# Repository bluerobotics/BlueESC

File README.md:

BlueESC
=======

The BlueESC is a simple, open-source electronic speed controller for three-phase brushless motors. It is designed to run the [SimonK firmware](http://github.com/sim-/tgy) on an Atmega8 microcontroller.

The hardware is licensed under GPLv3. It was inspired by and draws from other open-source ESC projects including [AfroESC](https://code.google.com/p/afrodevices/), [WiiESC](https://code.google.com/p/wii-esc/), and others. We owe a big thanks to everyone who has shared their open-source ESC designs and firmware.

We also thank Bernhard Konze and SimonK for the [tgy firmware](http://github.com/sim-/tgy). Please see the firmware license at the top of [tgy.asm](https://github.com/bluerobotics/tgy/blob/master/tgy.asm). The firmware configuration files for the BlueESC are maintained in [our fork of the tgy project](http://github.com/bluerobotics/tgy).

##Features

* Atmega8 microcontroller
* PWM and I2C signal interfaces
* 5-22 volt input (2-5s lipo)
* Reprogrammable via PWM pin using bootloader (usblinker)
* Status and warning LED indicators
* Sensors for voltage, current, temperature, and RPM
* No battery-eliminator-circuit (BEC)
* N-Channel MOSFETs

##Current Generation: Rev. 5-8

The current major revision is designed to work with the [BlueRobotics T100 Thruster](http://www.bluerobotics.com/thruster/). It is highly compact and is potted in an aluminum enclosure that acts as a heat sink. The board is built with two 2-layer boards, one for the power electronics and one for logic. The boards are connected by headers. This allows components to be placed on three sides, simplifies design, and minimizes cost.

###Features

* Hall effect current sense IC (ACS711EX)
* Thermistor temperature sensor (10K)

###Specifications

* 6-22 volt input
* 25 amps continuous current (air)
* 35+ amps continuous current (water)
* 400 uF decoupling capacitance
* Enclosure diameter: 40 mm (1.58")
* Enclosure length: 18.5 mm (0.73")

###Design Files

**Schematic:** [BlueESC.pdf](https://github.com/bluerobotics/BlueESC/raw/master/BlueESC/BlueESC.pdf)

See repository for up-to-date EagleCAD schematic and board layout.

##Firmware Compilation

The BlueESC uses the [tgy firmware located in the BlueRobotics fork](https://github.com/bluerobotics/tgy).

*Mac:* (Uses Homebrew)

```bash
brew update
brew install avra
make blueesc.hex
```

##Initial Firmware Flashing

The BlueESC can be flashed using any AVR ISP programmer.

```bash
avrdude -c [programmer] -p m8 -U flash:w:blueesc.hex:i 
```

The fuses should be set per the instructions in the [tgy](http://github.com/sim-/tgy) instructions.

```bash
avrdude -c [programmer] -p m8 -U lfuse:w:0x3f:m -U hfuse:w:0xca:m
```

The Rev5 version of the board does not include an ISP header or pads. The microcontroller must be flashed with a special tool that connects directly to the microcontroller pins. Make sure that the board is powered when programming.

##Firmware Flashing Through Bootloader

Once the ESC has had the firmware (including bootloader) flashed the first time, it can be reprogrammed subsequently through the PWM input pin using a programmer like the [Turnigy USB Linker](http://www.hobbyking.com/hobbyking/store/__10628__turnigy_usb_linker_for_aquastar_super_brain.html). This can be done through the Makefile in the **tgy** project as follows.

```bash
make program_tgy_blueesc
```

It can also be done with avrdude and the compiled hex files as follows.

```bash
avrdude -c stk500v2 -b 19200 -P [programmer port] -p m8 -U flash:w:blueesc.hex:i
```

##I2C Commands and Address

*Please also see our [Arduino library for I2C ESC control](https://github.com/bluerobotics/Arduino_I2C_ESC).*

The I2C message format allows speed and direction to be set and voltage, current, rpm, temperature, and status to be requested.

###Speed Command (Register 0x00-0x01)
* cmd: Command, sent as int16_t. Full range, negative for reverse, positive for forward.
  * Forward: 0 to 32767
  * Reverse: 0 to -32767

####Bytes
* Byte 0: throttle_h
* Byte 1: throttle_l

###Sensor Data (Register 0x02-0x0A)
* pulse_count: Commutation pulses since last request. Sent as uint16_t.
  * Calculate rpm with pulse_count/dt*60/motor_pole_count
* voltage: ADC measurement scaled to 16 bits
  * Calculate voltage with voltage/2016
* temperature: ADC measurement scaled to 16 bits
  * Calculate temperature with the Steinhart equation
* current: ADC measurement scaled to 16 bits
  * Calculate current with (current-32767)/891

####Bytes
* Byte 0: pulse_count_h
* Byte 1: pulse_count_l
* Byte 2: voltage_h
* Byte 3: voltage_l
* Byte 4: temperature_h
* Byte 5: temperature_l
* Byte 6: current_h
* Byte 7: current_l
* Byte 8: 0xab (identifier to check if ESC is alive)

##Releases

v1.0 - Rev5. Currently shipping.

v1.1 - Rev6. Added PWM pull-down resistor and low pass filter for current sense. Switched to SMT LEDs. No changes to Power Board.

##Video

I2C Demonstration:

Testing of Final Prototype:

Testing of First Prototype:

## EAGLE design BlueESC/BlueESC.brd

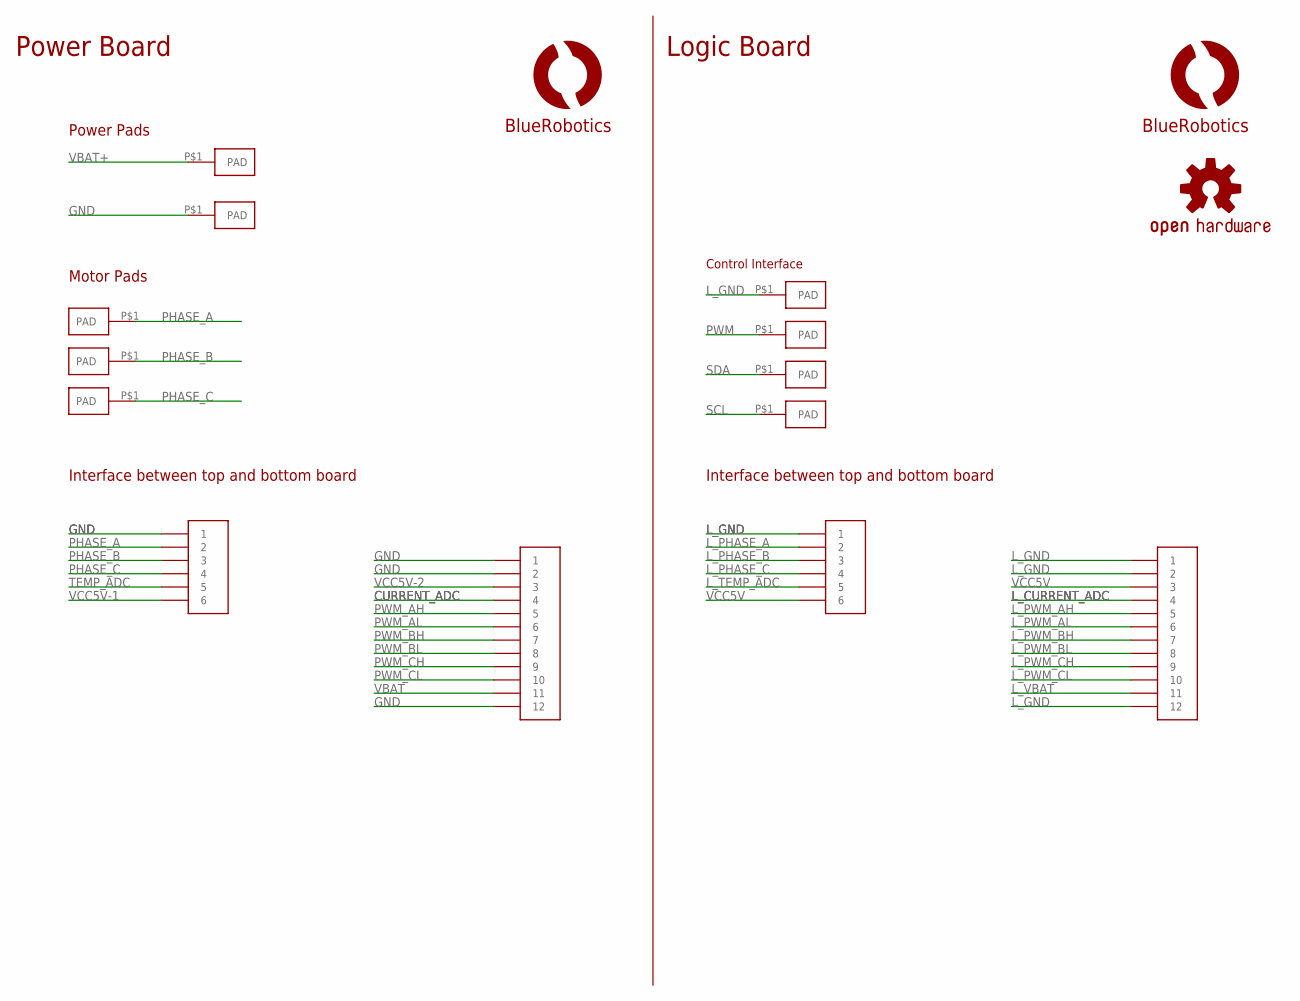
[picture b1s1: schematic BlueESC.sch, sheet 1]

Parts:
LOGO1: OSHW-LOGOS; OSHW-LOGO-S
U$1, U$2: PADPTH-MED; PAD-PTH-MED-1
U$4, U$16: HEADER-62MM; HEADER-2MM-6POS
U$5, U$6, U$7: PAD18AWG; PAD-PTH-18AWG-1
U$8, U$17: HEADER-122MM; HEADER-2MM-12POS
U$9: LOGOBR-LOGO-S; BR-LOGO-SMALL
U$10: LOGOBR-LOGO-M; BR-LOGO-MEDIUM
U$11, U$12, U$13, U$14: PAD1.5X3MM; PAD-1.5X3MM

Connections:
CURRENT_ADC: U$8.P$4 (4); also elsewhere on the board
GND: U$2.P$1, U$4.P$1 (1), U$8.P$1 (1), U$8.P$2 (2), U$8.P$12 (12); also elsewhere on the board
L_CURRENT_ADC: U$17.P$4 (4); also elsewhere on the board
L_GND: U$11.P$1, U$16.P$1 (1), U$17.P$1 (1), U$17.P$2 (2), U$17.P$12 (12); also elsewhere on the board
L_PHASE_A: U$16.P$2 (2); also elsewhere on the board
L_PHASE_B: U$16.P$3 (3); also elsewhere on the board
L_PHASE_C: U$16.P$4 (4); also elsewhere on the board
L_PWM_AH: U$17.P$5 (5); also elsewhere on the board
L_PWM_AL: U$17.P$6 (6); also elsewhere on the board
L_PWM_BH: U$17.P$7 (7); also elsewhere on the board
L_PWM_BL: U$17.P$8 (8); also elsewhere on the board
L_PWM_CH: U$17.P$9 (9); also elsewhere on the board
L_PWM_CL: U$17.P$10 (10); also elsewhere on the board
L_TEMP_ADC: U$16.P$5 (5); also elsewhere on the board
L_VBAT: U$17.P$11 (11); also elsewhere on the board
PHASE_A: U$4.P$2 (2), U$5.P$1; also elsewhere on the board
PHASE_B: U$4.P$3 (3), U$6.P$1; also elsewhere on the board
PHASE_C: U$4.P$4 (4), U$7.P$1; also elsewhere on the board
PWM: U$14.P$1; also elsewhere on the board
PWM_AH: U$8.P$5 (5); also elsewhere on the board
PWM_AL: U$8.P$6 (6); also elsewhere on the board
PWM_BH: U$8.P$7 (7); also elsewhere on the board
PWM_BL: U$8.P$8 (8); also elsewhere on the board
PWM_CH: U$8.P$9 (9); also elsewhere on the board
PWM_CL: U$8.P$10 (10); also elsewhere on the board
SCL: U$13.P$1; also elsewhere on the board
SDA: U$12.P$1; also elsewhere on the board
TEMP_ADC: U$4.P$5 (5); also elsewhere on the board
VBAT: U$8.P$11 (11); also elsewhere on the board
VBAT+: U$1.P$1; also elsewhere on the board
VCC5V: U$16.P$6 (6), U$17.P$3 (3); also elsewhere on the board
VCC5V-1: U$4.P$6 (6); also elsewhere on the board
VCC5V-2: U$8.P$3 (3); also elsewhere on the board

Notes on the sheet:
Power Pads
Motor Pads
Interface between top and bottom board
Control Interface
Power Board
Logic Board

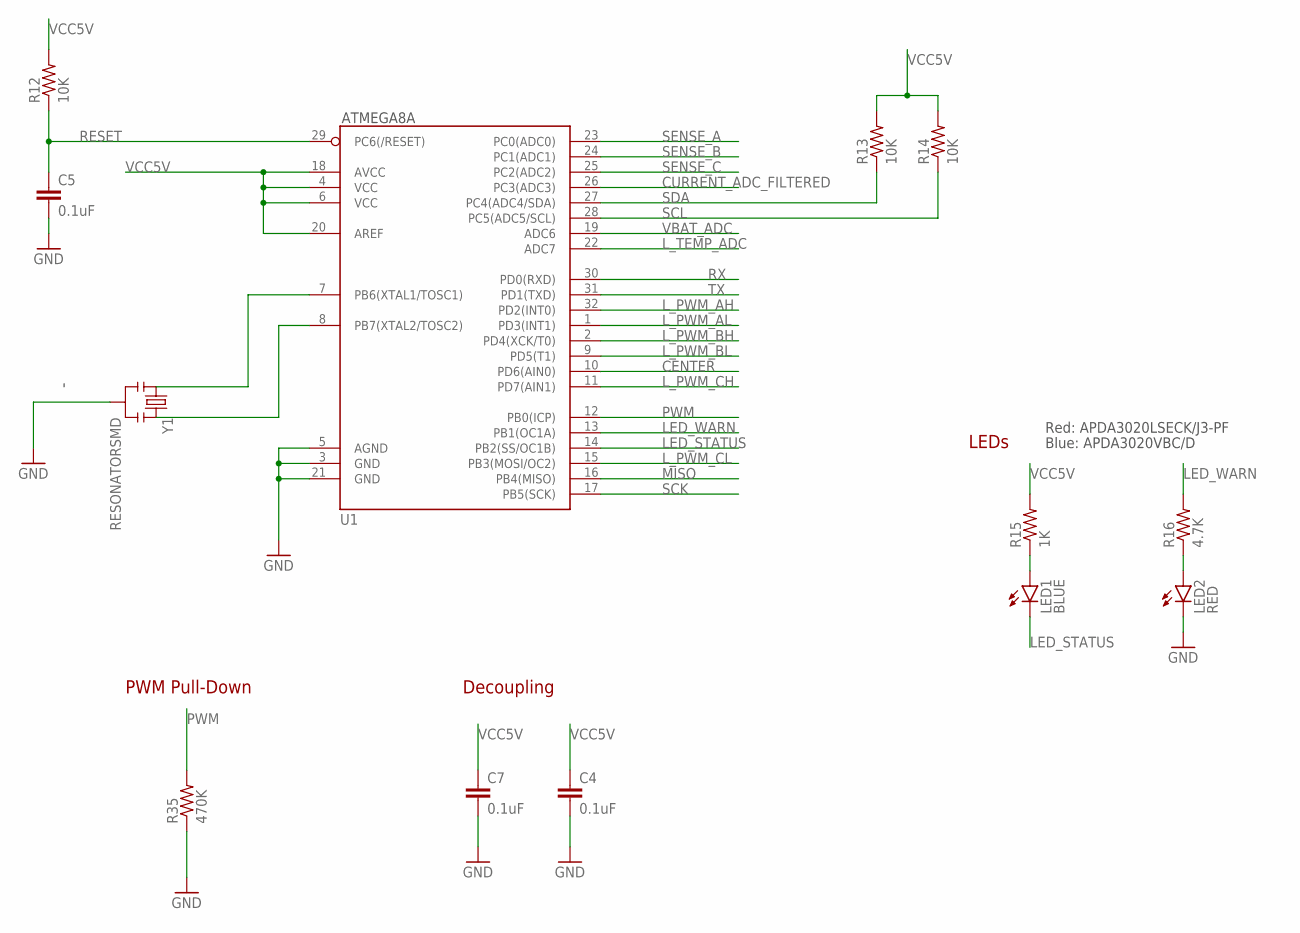
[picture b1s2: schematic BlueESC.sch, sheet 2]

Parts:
C4, C5, C7: 0.1uF; 0603-CAP
LED1: BLUE; SMT-LED-3X2-RA
LED2: RED; SMT-LED-3X2-RA
R12, R13, R14: 10K; 0603-RES
R15: 1K; 0603-RES
R16: 4.7K; 0603-RES
R35: 470K; 0603-RES
U1: ATMEGA168; TQFP32-08
Y1: RESONATORSMD; RESONATOR-SMD

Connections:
CENTER: U1.10 (PD6(AIN0)); also elsewhere on the board
CURRENT_ADC_FILTERED: U1.26 (PC3(ADC3)); also elsewhere on the board
LED_STATUS: LED1.2 (C), U1.14 (PB2(SS/OC1B))
LED_WARN: R16.2, U1.13 (PB1(OC1A))
L_GND: C4.2, C5.2, C7.2, LED2.2 (C), R35.1, U1.3 (GND), U1.5 (AGND), U1.21 (GND), Y1.2; also elsewhere on the board
L_PWM_AH: U1.32 (PD2(INT0)); also elsewhere on the board
L_PWM_AL: U1.1 (PD3(INT1)); also elsewhere on the board
L_PWM_BH: U1.2 (PD4(XCK/T0)); also elsewhere on the board
L_PWM_BL: U1.9 (PD5(T1)); also elsewhere on the board
L_PWM_CH: U1.11 (PD7(AIN1)); also elsewhere on the board
L_PWM_CL: U1.15 (PB3(MOSI/OC2)); also elsewhere on the board
L_TEMP_ADC: U1.22 (ADC7); also elsewhere on the board
MISO: U1.16 (PB4(MISO))
unnamed: LED2.1 (A), R16.1
unnamed: U1.7 (PB6(XTAL1/TOSC1)), Y1.1
unnamed: U1.8 (PB7(XTAL2/TOSC2)), Y1.3
unnamed: LED1.1 (A), R15.1
PWM: R35.2, U1.12 (PB0(ICP)); also elsewhere on the board
RESET: C5.1, R12.1, U1.29 (PC6(/RESET))
RX: U1.30 (PD0(RXD))
SCK: U1.17 (PB5(SCK))
SCL: R14.1, U1.28 (PC5(ADC5/SCL)); also elsewhere on the board
SDA: R13.1, U1.27 (PC4(ADC4/SDA)); also elsewhere on the board
SENSE_A: U1.23 (PC0(ADC0)); also elsewhere on the board
SENSE_B: U1.24 (PC1(ADC1)); also elsewhere on the board
SENSE_C: U1.25 (PC2(ADC2)); also elsewhere on the board
TX: U1.31 (PD1(TXD))
VBAT_ADC: U1.19 (ADC6); also elsewhere on the board
VCC5V: C4.1, C7.1, R12.2, R13.2, R14.2, R15.2, U1.4 (VCC), U1.6 (VCC), U1.18 (AVCC), U1.20 (AREF); also elsewhere on the board

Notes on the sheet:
ATMEGA8A
Decoupling
LEDs
Red: APDA3020LSECK/J3-PF
Blue: APDA3020VBC/D
PWM Pull-Down

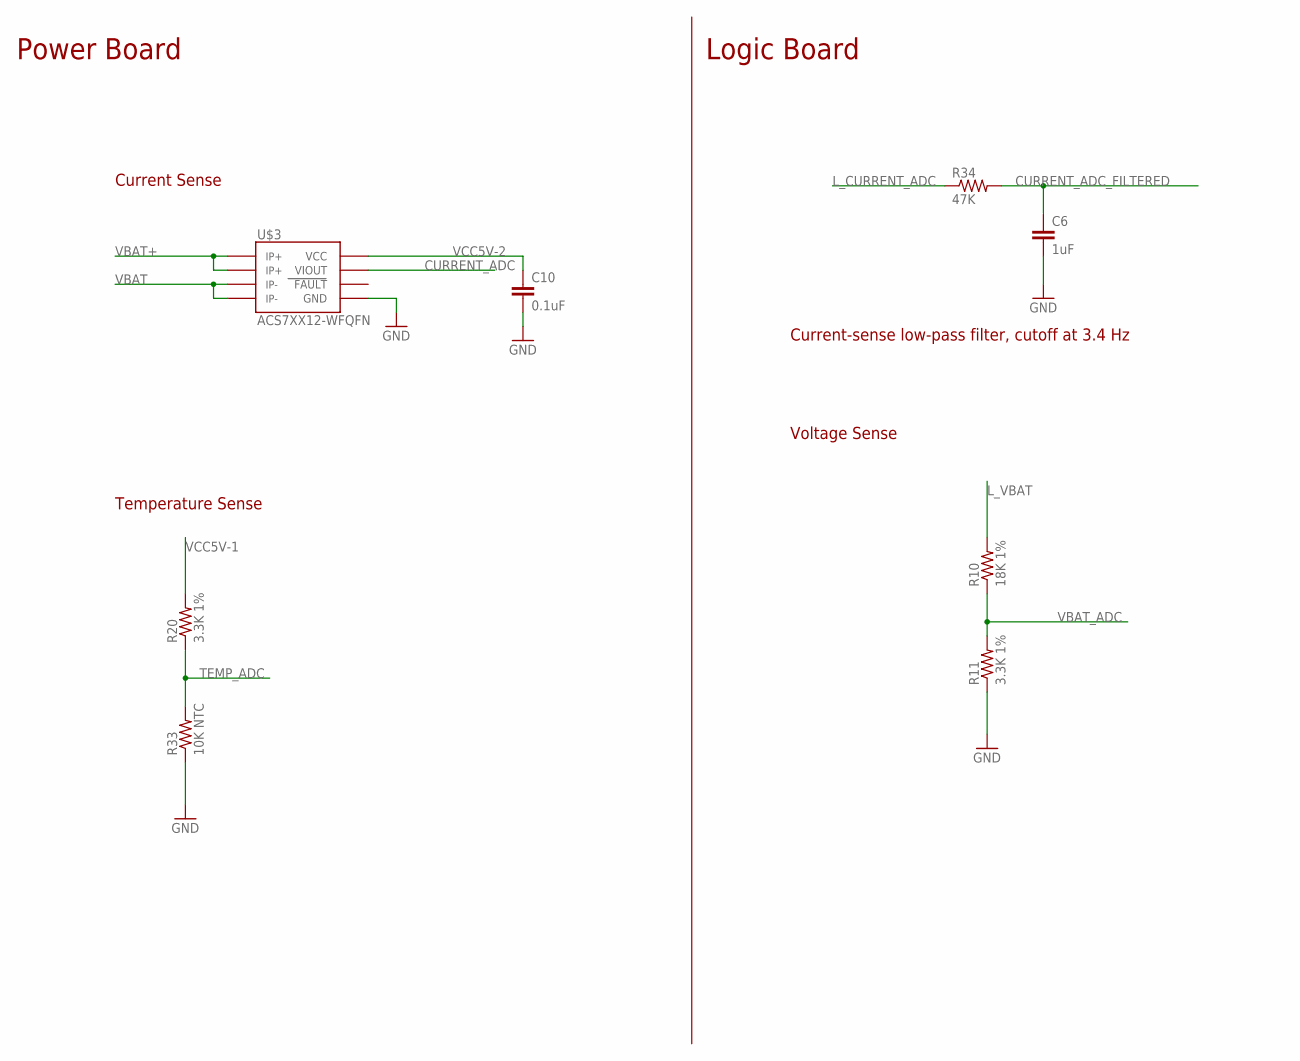
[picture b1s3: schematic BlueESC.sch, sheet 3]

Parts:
C6: 1uF; 0603-CAP
C10: 0.1uF; 0603-CAP
R10: 18K 1%; 0603-RES
R11, R20: 3.3K 1%; 0603-RES
R33: 10K NTC; 0603-RES
R34: 47K; 0603-RES
U$3: ACS7XX12-WFQFN; 12-WFQFN

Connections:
CURRENT_ADC: U$3.VIOUT; also elsewhere on the board
CURRENT_ADC_FILTERED: C6.1, R34.2; also elsewhere on the board
GND: C10.2, R33.1, U$3.GND; also elsewhere on the board
L_CURRENT_ADC: R34.1; also elsewhere on the board
L_GND: C6.2, R11.1; also elsewhere on the board
L_VBAT: R10.2; also elsewhere on the board
TEMP_ADC: R20.1, R33.2; also elsewhere on the board
VBAT: U$3.IP-1, U$3.IP-2; also elsewhere on the board
VBAT+: U$3.IP+1, U$3.IP+2; also elsewhere on the board
VBAT_ADC: R10.1, R11.2; also elsewhere on the board
VCC5V-1: R20.2; also elsewhere on the board
VCC5V-2: C10.1, U$3.VCC; also elsewhere on the board

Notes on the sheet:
Power Board
Logic Board
Current-sense low-pass filter, cutoff at 3.4 Hz
Voltage Sense
Current Sense
Temperature Sense

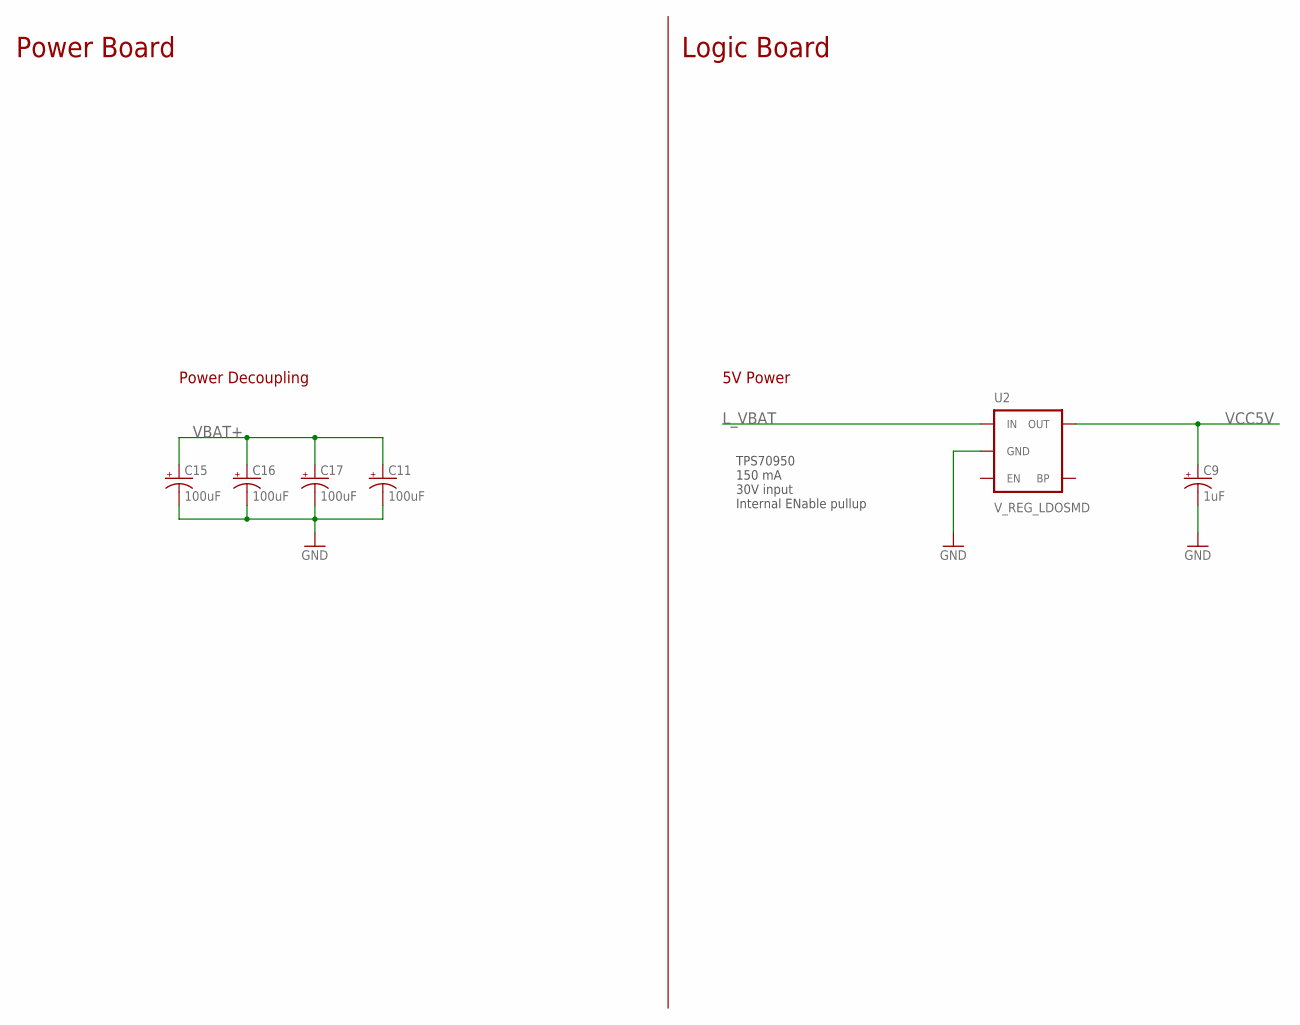
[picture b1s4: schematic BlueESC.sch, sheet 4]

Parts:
C9: 1uF; EIA3216
C11, C15, C16, C17: 100uF; EIA7343
U2: V_REG_LDOSMD; SOT23-5

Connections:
GND: C11.C (-), C15.C (-), C16.C (-), C17.C (-); also elsewhere on the board
L_GND: C9.C (-), U2.2 (GND); also elsewhere on the board
L_VBAT: U2.1 (IN); also elsewhere on the board
VBAT+: C11.A (+), C15.A (+), C16.A (+), C17.A (+); also elsewhere on the board
VCC5V: C9.A (+), U2.5 (OUT); also elsewhere on the board

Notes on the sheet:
Power Board
Logic Board
Power Decoupling
5V Power
TPS70950 150 mA 30V input Internal ENable pullup

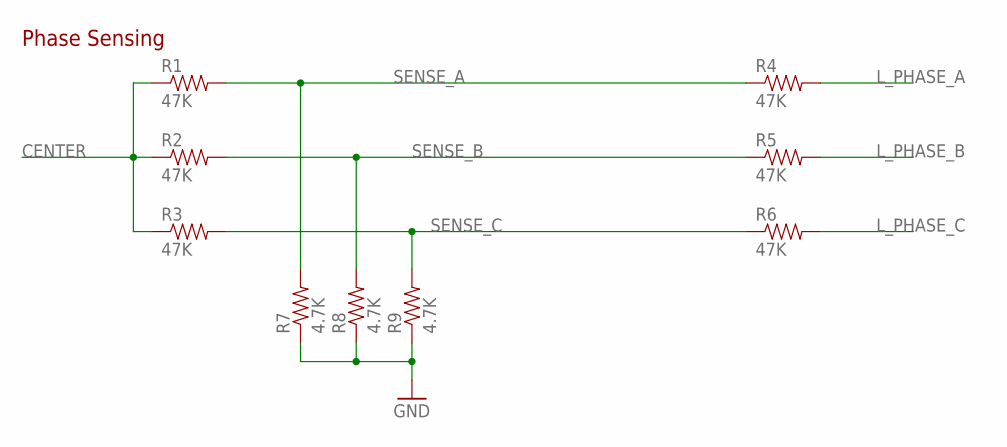
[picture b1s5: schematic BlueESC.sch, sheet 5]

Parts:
R1, R2, R3, R4, R5, R6: 47K; 0603-RES
R7, R8, R9: 4.7K; 0603-RES

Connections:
CENTER: R1.1, R2.1, R3.1; also elsewhere on the board
L_GND: R7.1, R8.1, R9.1; also elsewhere on the board
L_PHASE_A: R4.2; also elsewhere on the board
L_PHASE_B: R5.2; also elsewhere on the board
L_PHASE_C: R6.2; also elsewhere on the board
SENSE_A: R1.2, R4.1, R7.2; also elsewhere on the board
SENSE_B: R2.2, R5.1, R8.2; also elsewhere on the board
SENSE_C: R3.2, R6.1, R9.2; also elsewhere on the board

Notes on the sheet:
Phase Sensing

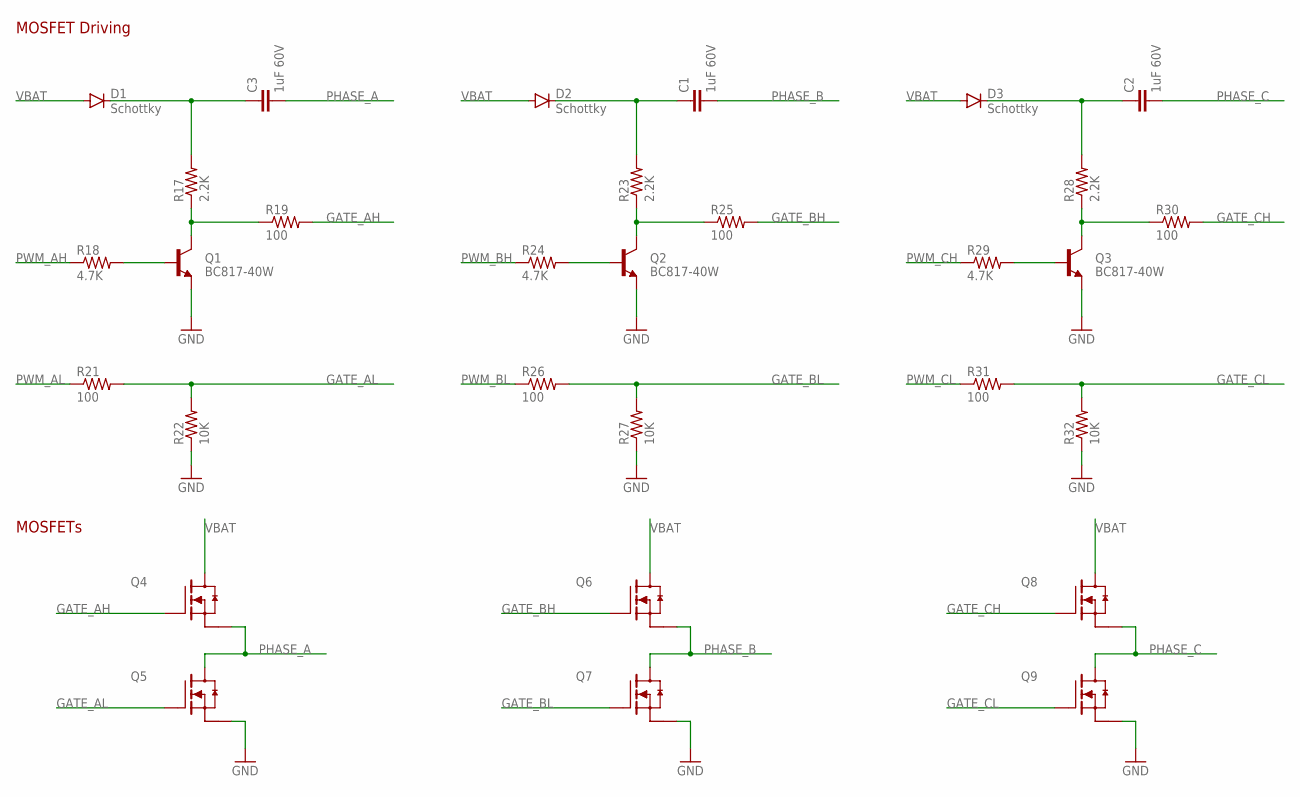
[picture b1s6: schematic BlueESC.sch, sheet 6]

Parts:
C1, C2, C3: 1uF 60V; 0805
D1, D2, D3: Schottky; SOD-323
Q1, Q2, Q3: BC817-40W; SOT23
Q4, Q5, Q6, Q7, Q8, Q9: MOSFET-NCHANNEL; TDSON-8
R17, R23, R28: 2.2K; 0603-RES
R18, R24, R29: 4.7K; 0603-RES
R19, R21, R25, R26, R30, R31: 100; 0603-RES
R22, R27, R32: 10K; 0603-RES

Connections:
GATE_AH: Q4.G, R19.2
GATE_AL: Q5.G, R21.2, R22.2
GATE_BH: Q6.G, R25.2
GATE_BL: Q7.G, R26.2, R27.2
GATE_CH: Q8.G, R30.2
GATE_CL: Q9.G, R31.2, R32.2
GND: Q1.2 (E), Q2.2 (E), Q3.2 (E), Q5.S1 (S), Q5.S2 (S), Q5.S3 (S), Q7.S1 (S), Q7.S2 (S), Q7.S3 (S), Q9.S1 (S), Q9.S2 (S), Q9.S3 (S), R22.1, R27.1, R32.1; also elsewhere on the board
unnamed: Q1.1 (B), R18.2
unnamed: Q1.3 (C), R17.1, R19.1
unnamed: Q2.1 (B), R24.2
unnamed: Q2.3 (C), R23.1, R25.1
unnamed: Q3.1 (B), R29.2
unnamed: Q3.3 (C), R28.1, R30.1
unnamed: C3.1, D1.C, R17.2
unnamed: C1.1, D2.C, R23.2
unnamed: C2.1, D3.C, R28.2
PHASE_A: C3.2, Q4.S1 (S), Q4.S2 (S), Q4.S3 (S), Q5.D; also elsewhere on the board
PHASE_B: C1.2, Q6.S1 (S), Q6.S2 (S), Q6.S3 (S), Q7.D; also elsewhere on the board
PHASE_C: C2.2, Q8.S1 (S), Q8.S2 (S), Q8.S3 (S), Q9.D; also elsewhere on the board
PWM_AH: R18.1; also elsewhere on the board
PWM_AL: R21.1; also elsewhere on the board
PWM_BH: R24.1; also elsewhere on the board
PWM_BL: R26.1; also elsewhere on the board
PWM_CH: R29.1; also elsewhere on the board
PWM_CL: R31.1; also elsewhere on the board
VBAT: D1.A, D2.A, D3.A, Q4.D, Q6.D, Q8.D; also elsewhere on the board

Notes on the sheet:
MOSFETs
MOSFET Driving

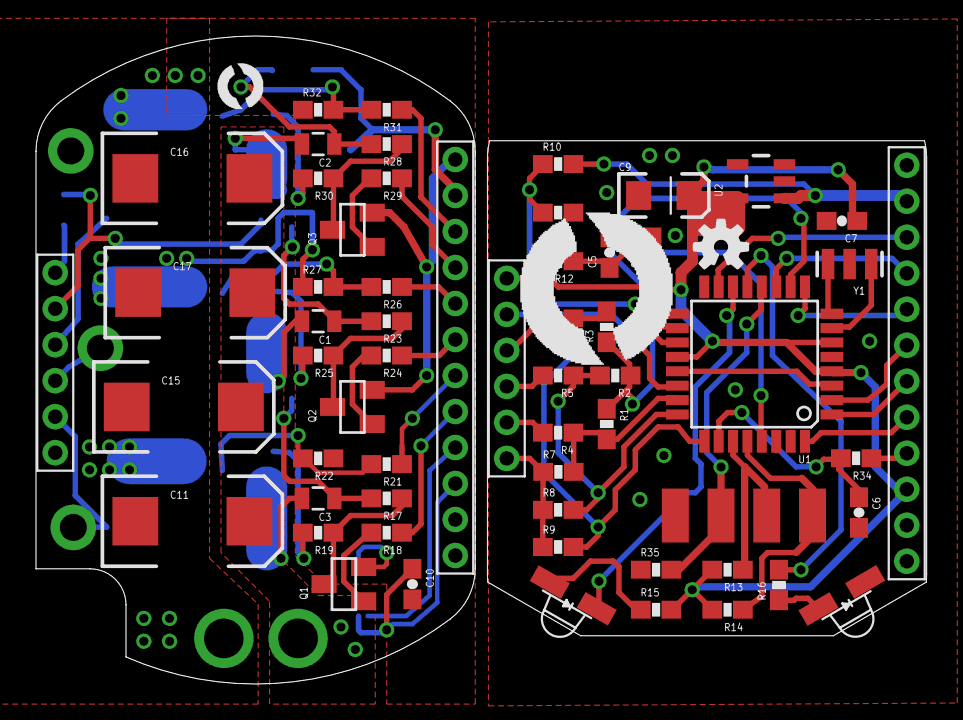
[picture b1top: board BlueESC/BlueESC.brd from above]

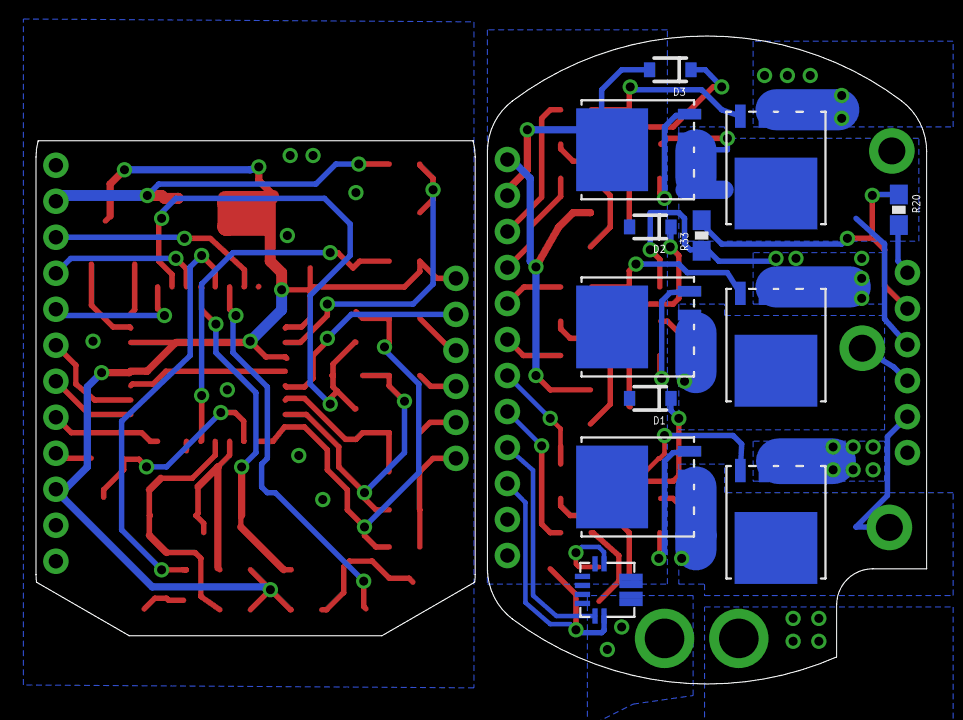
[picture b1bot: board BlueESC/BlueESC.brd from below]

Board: 2 copper layers, 49.5 x 36.0 mm, 82 parts (15 on the bottom side), 61 nets.

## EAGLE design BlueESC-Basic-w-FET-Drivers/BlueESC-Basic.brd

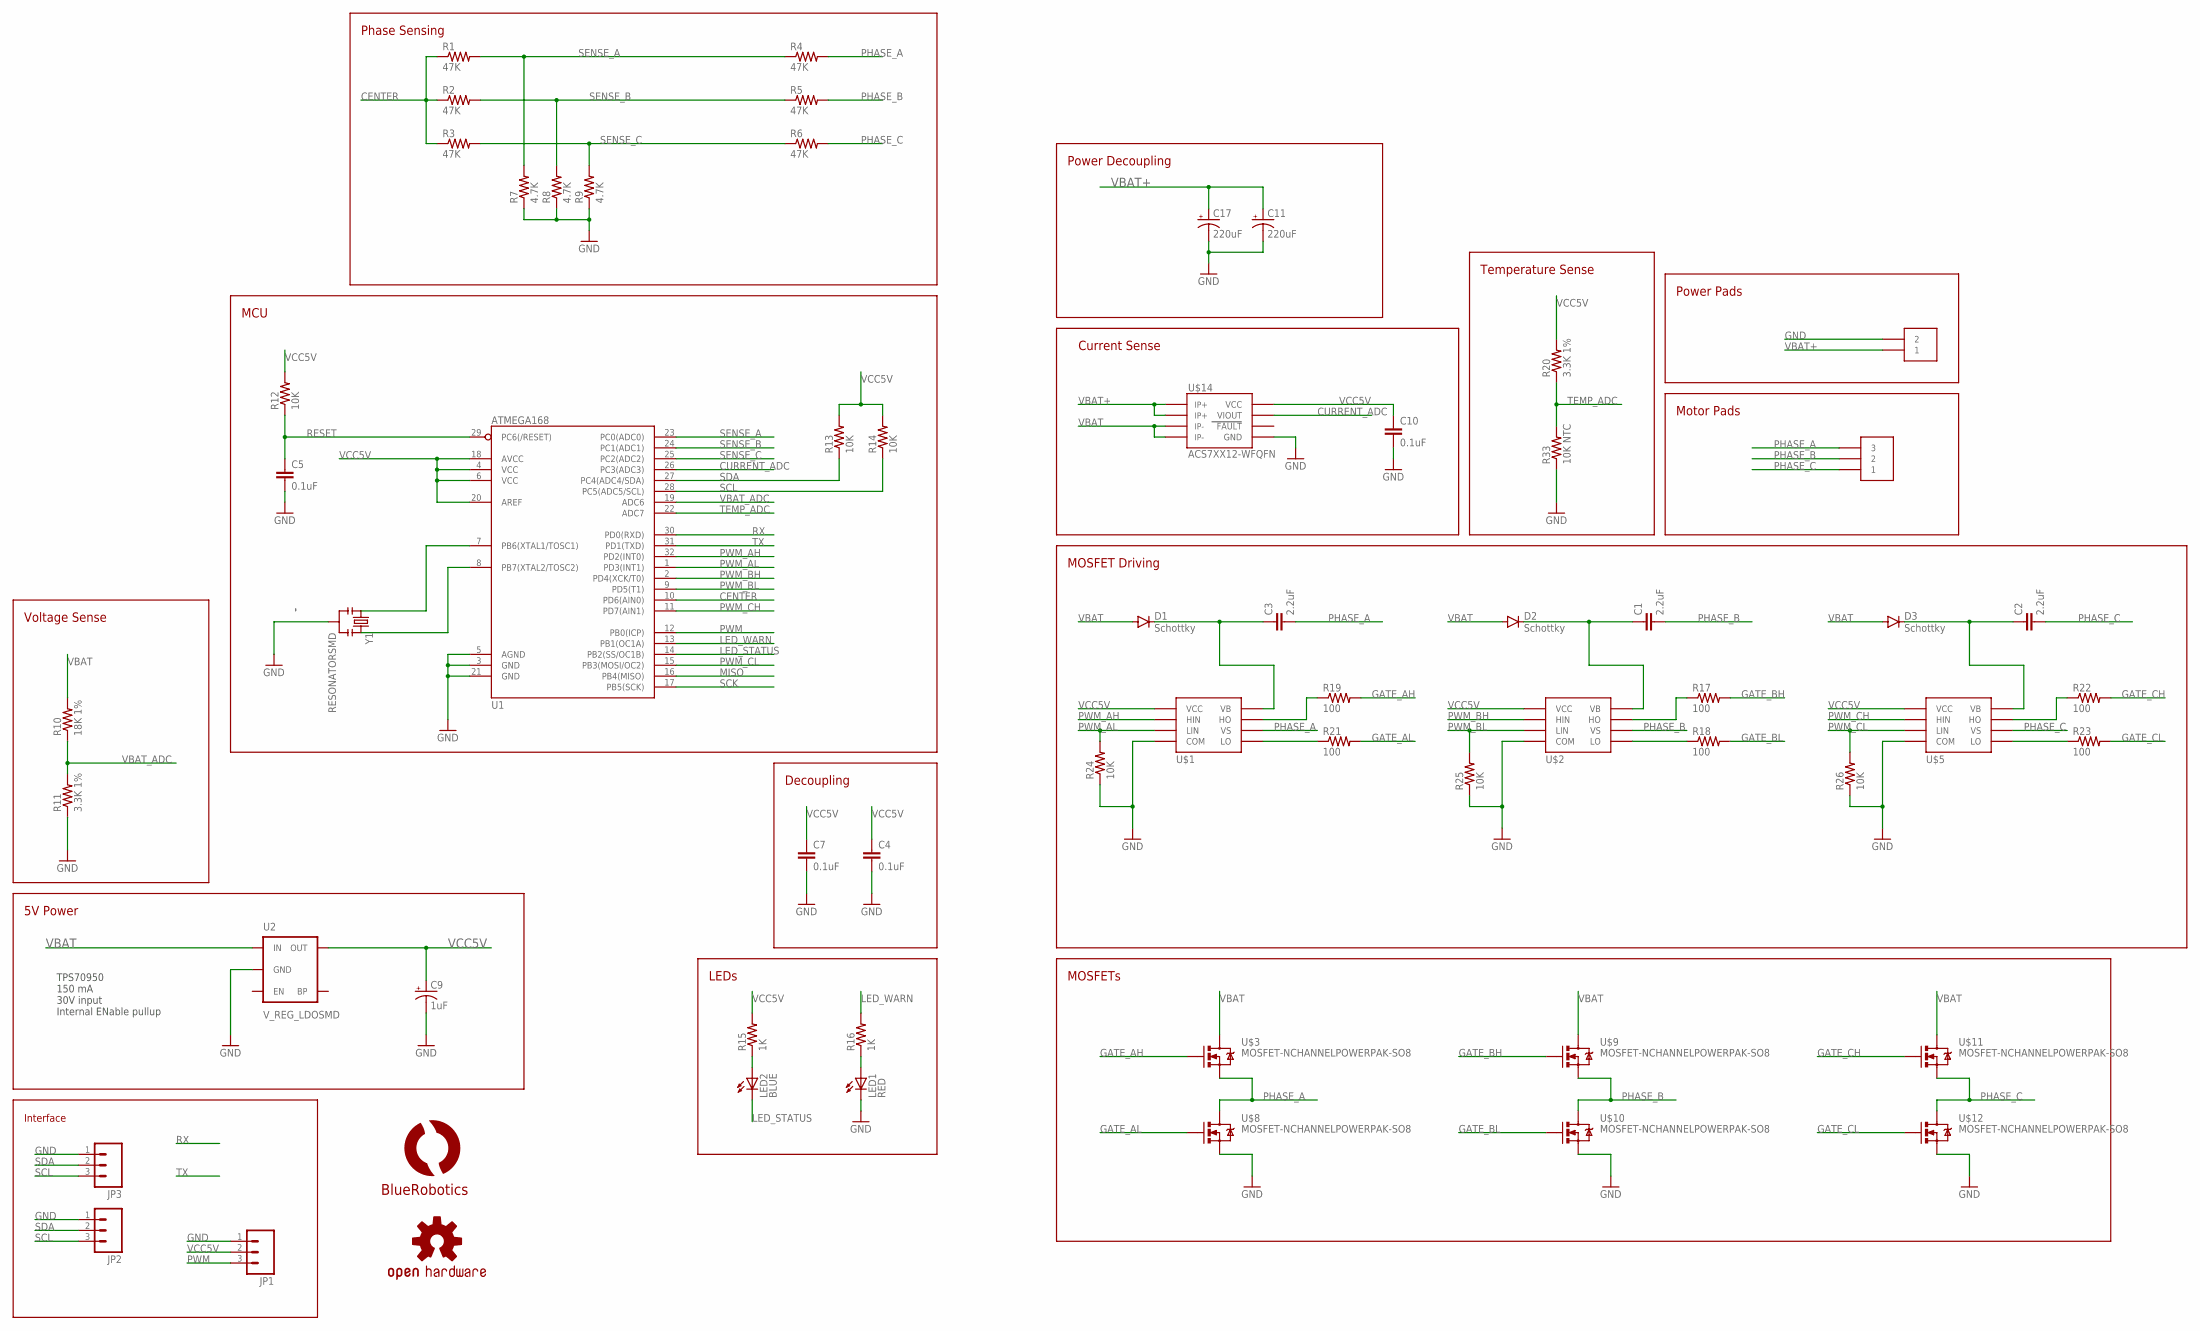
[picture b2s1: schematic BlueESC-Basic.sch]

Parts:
C1, C2, C3: 2.2uF; 0805
C4, C5, C7, C10: 0.1uF; 0603-CAP
C9: 1uF; EIA3216
C11, C17: 220uF; PANASONIC_E
D1, D2, D3: Schottky; SOD-323
JP1, JP2, JP3: M03PTH; 1X03
LED1: RED; LED-0603
LED2: BLUE; LED-0603
LOGO1: OSHW-LOGOS; OSHW-LOGO-S
R1, R2, R3, R4, R5, R6: 47K; 0603-RES
R7, R8, R9: 4.7K; 0603-RES
R10: 18K 1%; 0603-RES
R11, R20: 3.3K 1%; 0603-RES
R12, R13, R14, R24, R25, R26: 10K; 0603-RES
R15, R16: 1K; 0603-RES
R17, R18, R19, R21, R22, R23: 100; 0603-RES
R33: 10K NTC; 0603-RES
U1: ATMEGA168; TQFP32-08
U2: V_REG_LDOSMD; SOT23-5
U$1, U$2, U$5: IR2101SOIC8; SOIC8
U$3, U$8, U$9, U$10, U$11, U$12: MOSFET-NCHANNELPOWERPAK-SO8; POWERPAK-SO8
U$4: LOGOBR-LOGO-M; BR-LOGO-MEDIUM
U$14: ACS7XX12-WFQFN; 12-WFQFN
U$15: HEADER-2BARRIER-BLOCK-1; OSTYK33102030
U$16: HEADER-3BARRIER-BLOCK-1; OSTYK33103030
Y1: RESONATORSMD; RESONATOR-SMD

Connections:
CENTER: R1.1, R2.1, R3.1, U1.10 (PD6(AIN0))
CURRENT_ADC: U1.26 (PC3(ADC3)), U$14.VIOUT
GATE_AH: R19.2, U$3.4 (G)
GATE_AL: R21.2, U$8.4 (G)
GATE_BH: R17.2, U$9.4 (G)
GATE_BL: R18.2, U$10.4 (G)
GATE_CH: R22.2, U$11.4 (G)
GATE_CL: R23.2, U$12.4 (G)
GND: C4.2, C5.2, C7.2, C9.C (-), C10.2, C11.-, C17.-, JP2.1, JP3.1, LED1.C, R7.1, R8.1, R9.1, R11.1, R24.1, R25.1, R26.1, R33.1, U1.3 (GND), U1.5 (AGND), U1.21 (GND), U2.2 (GND), U$1.4 (COM), U$2.4 (COM), U$5.4 (COM), U$8.1 (S), U$8.2 (S), U$8.3 (S), U$10.1 (S), U$10.2 (S), U$10.3 (S), U$12.1 (S), U$12.2 (S), U$12.3 (S), U$14.GND, U$15.2, Y1.2
LED_STATUS: LED2.C, U1.14 (PB2(SS/OC1B))
LED_WARN: R16.2, U1.13 (PB1(OC1A))
MISO: U1.16 (PB4(MISO))
unnamed: C1.1, D2.C, U$2.8 (VB)
unnamed: R19.1, U$1.7 (HO)
unnamed: LED1.A, R16.1
unnamed: R21.1, U$1.5 (LO)
unnamed: R17.1, U$2.7 (HO)
unnamed: R18.1, U$2.5 (LO)
unnamed: C2.1, D3.C, U$5.8 (VB)
unnamed: R22.1, U$5.7 (HO)
unnamed: R23.1, U$5.5 (LO)
unnamed: U1.7 (PB6(XTAL1/TOSC1)), Y1.1
unnamed: U1.8 (PB7(XTAL2/TOSC2)), Y1.3
unnamed: C3.1, D1.C, U$1.8 (VB)
unnamed: LED2.A, R15.1
PHASE_A: C3.2, R4.2, U$1.6 (VS), U$3.1 (S), U$3.2 (S), U$3.3 (S), U$8.5 (D), U$8.6 (D), U$8.7 (D), U$8.8 (D), U$8.9 (D), U$16.3
PHASE_B: C1.2, R5.2, U$2.6 (VS), U$9.1 (S), U$9.2 (S), U$9.3 (S), U$10.5 (D), U$10.6 (D), U$10.7 (D), U$10.8 (D), U$10.9 (D), U$16.2
PHASE_C: C2.2, R6.2, U$5.6 (VS), U$11.1 (S), U$11.2 (S), U$11.3 (S), U$12.5 (D), U$12.6 (D), U$12.7 (D), U$12.8 (D), U$12.9 (D), U$16.1
PWM: U1.12 (PB0(ICP))
PWM_AH: U1.32 (PD2(INT0)), U$1.2 (HIN)
PWM_AL: R24.2, U1.1 (PD3(INT1)), U$1.3 (LIN)
PWM_BH: U1.2 (PD4(XCK/T0)), U$2.2 (HIN)
PWM_BL: R25.2, U1.9 (PD5(T1)), U$2.3 (LIN)
PWM_CH: U1.11 (PD7(AIN1)), U$5.2 (HIN)
PWM_CL: R26.2, U1.15 (PB3(MOSI/OC2)), U$5.3 (LIN)
RESET: C5.1, R12.1, U1.29 (PC6(/RESET))
RX: U1.30 (PD0(RXD))
SCK: U1.17 (PB5(SCK))
SCL: JP2.3, JP3.3, R14.1, U1.28 (PC5(ADC5/SCL))
SDA: JP2.2, JP3.2, R13.1, U1.27 (PC4(ADC4/SDA))
SENSE_A: R1.2, R4.1, R7.2, U1.23 (PC0(ADC0))
SENSE_B: R2.2, R5.1, R8.2, U1.24 (PC1(ADC1))
SENSE_C: R3.2, R6.1, R9.2, U1.25 (PC2(ADC2))
TEMP_ADC: R20.1, R33.2, U1.22 (ADC7)
TX: U1.31 (PD1(TXD))
VBAT: D1.A, D2.A, D3.A, R10.2, U2.1 (IN), U$3.5 (D), U$3.6 (D), U$3.7 (D), U$3.8 (D), U$3.9 (D), U$9.5 (D), U$9.6 (D), U$9.7 (D), U$9.8 (D), U$9.9 (D), U$11.5 (D), U$11.6 (D), U$11.7 (D), U$11.8 (D), U$11.9 (D), U$14.IP-1, U$14.IP-2
VBAT+: C11.+, C17.+, U$14.IP+1, U$14.IP+2, U$15.1
VBAT_ADC: R10.1, R11.2, U1.19 (ADC6)
VCC5V: C4.1, C7.1, C9.A (+), C10.1, R12.2, R13.2, R14.2, R15.2, R20.2, U1.4 (VCC), U1.6 (VCC), U1.18 (AVCC), U1.20 (AREF), U2.5 (OUT), U$1.1 (VCC), U$2.1 (VCC), U$5.1 (VCC), U$14.VCC

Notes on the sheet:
MCU
Decoupling
LEDs
Phase Sensing
Voltage Sense
5V Power
Interface
TPS70950 150 mA 30V input Internal ENable pullup
MOSFET Driving
MOSFETs
Power Decoupling
Power Pads
Motor Pads
Current Sense
Temperature Sense

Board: 2 copper layers, 62 parts (23 on the bottom side), 44 nets, no tracks yet.

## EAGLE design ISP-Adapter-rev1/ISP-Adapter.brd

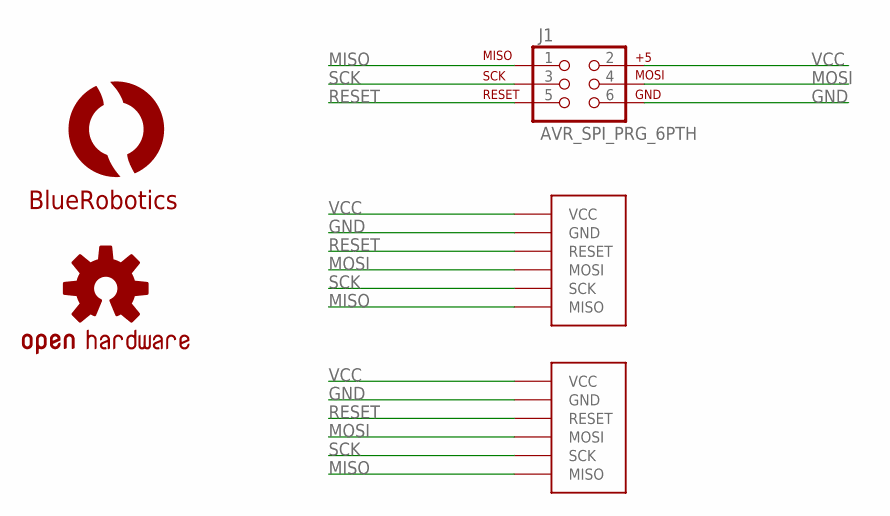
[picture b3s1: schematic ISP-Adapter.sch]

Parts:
J1: AVR_SPI_PRG_6PTH; 2X3
LOGO1: OSHW-LOGOS; OSHW-LOGO-S
U$1: AVR-ISPTINY-SMD; AVR-ISP-TINY
U$2: AVR-ISPTINY-SMD-POGO; AVR-ISP-TINY-POGO
U$3: LOGOBR-LOGO-S; BR-LOGO-SMALL

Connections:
GND: J1.6, U$1.GND, U$2.GND
MISO: J1.1, U$1.MISO, U$2.MISO
MOSI: J1.4, U$1.MOSI, U$2.MOSI
RESET: J1.5, U$1.RESET, U$2.RESET
SCK: J1.3, U$1.SCK, U$2.SCK
VCC: J1.2, U$1.VCC, U$2.VCC

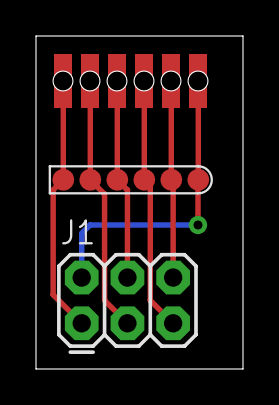
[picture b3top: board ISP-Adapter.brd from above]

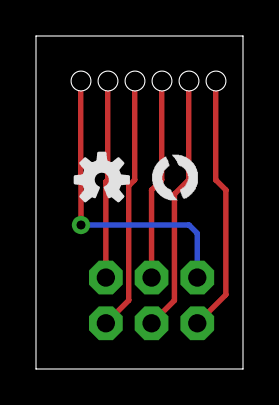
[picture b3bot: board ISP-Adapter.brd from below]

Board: 2 copper layers, 11.5 x 18.5 mm, 5 parts (2 on the bottom side), 6 nets.

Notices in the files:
parts and their libraries:
SparkFun-Capacitors: Licensing: Creative Commons ShareAlike 4.0 International - https://creativecommons.org/licenses/by-sa/4.0
